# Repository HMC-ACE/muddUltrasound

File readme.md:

Low-Cost Underwater Ultrasonic Phased Array Research Platform
-------------------------------------------------------------

This repo contains all PCB designs, SAM4s MCU firmware, python imaging code, and documentation for the phased array research platform.

For full documentation, see [link](doc/build/html/index.html) (in a browser, you'll need to clone the repo first).

Directory
--------
 - `doc` contains the documentation source and build files (using sphinx).
 - `pcb` contains the KiCad PCB files for the channel boards and center board.
 - `mcu` contains the Atmel Studio project files for the MCU firmware.
 - `scripts` contains all python scripts to be run on the host computer.

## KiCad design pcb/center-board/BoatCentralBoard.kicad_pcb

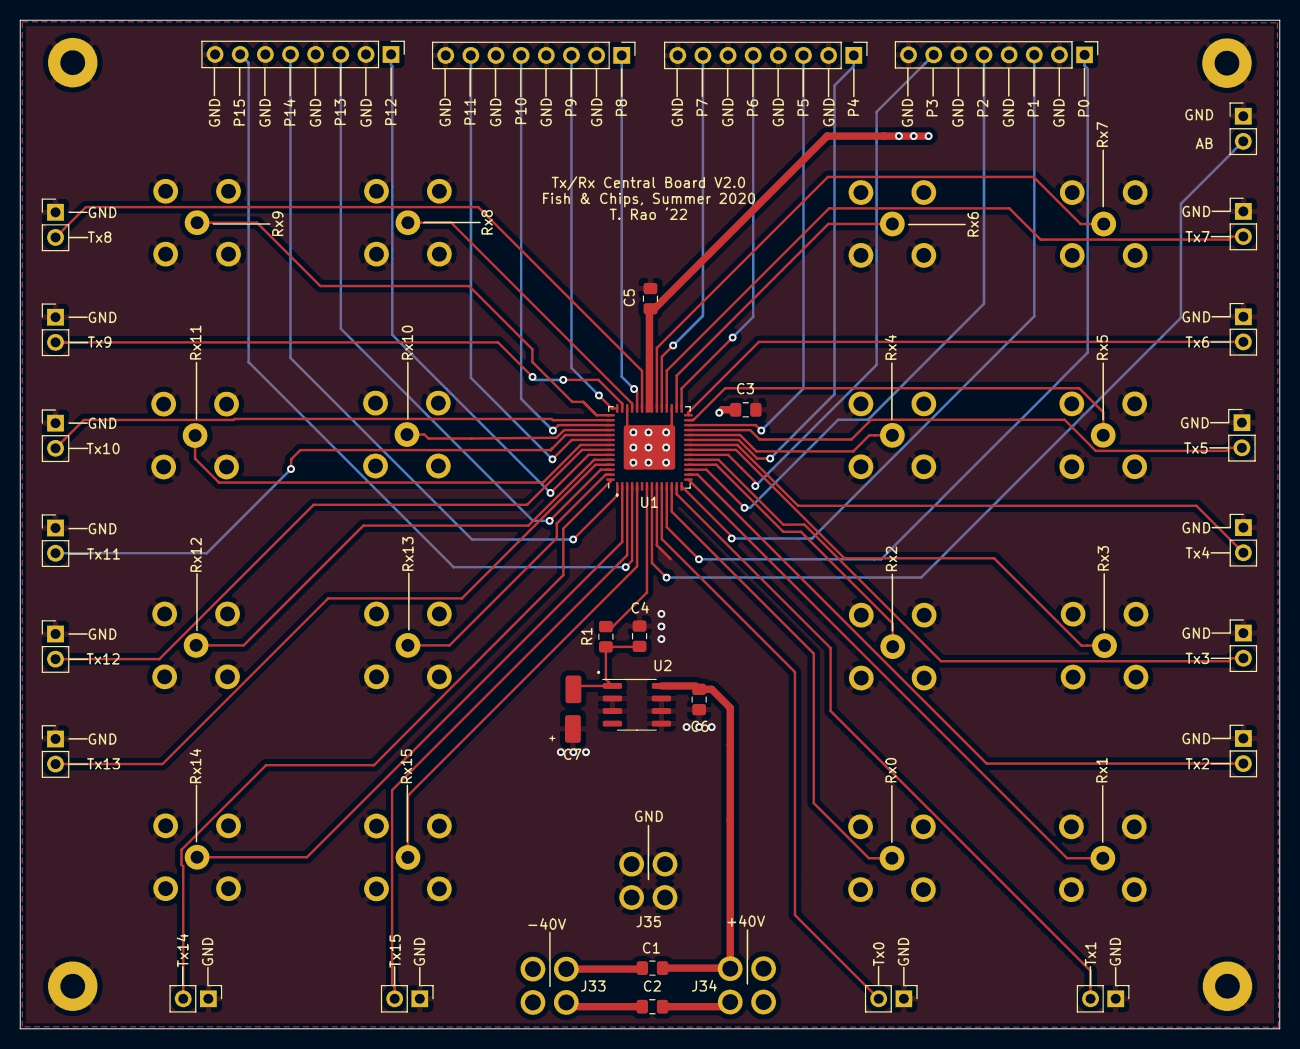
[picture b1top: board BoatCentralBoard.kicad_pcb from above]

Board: 4 copper layers, 127.2 x 101.9 mm, 50 parts (0 on the bottom side), 54 nets.

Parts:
C1: 1μF; C_0805_2012Metric_Pad1.15x1.40mm_HandSolder
C2, C3, C4, C5: 0.1μF; C_0805_2012Metric_Pad1.15x1.40mm_HandSolder
C6: 0.1uF; C_0805_2012Metric_Pad1.15x1.40mm_HandSolder
C7: 47uF; 47uFBypass
J1, J3, J5, J7, J9, J11, J13, J15, J17, J19, J21, J23, J25, J27, J29, J31: Screw_Terminal_01x02; PinHeader_1x02_P2.54mm_Vertical
J2, J4, J6, J8, J10, J12, J14, J16, J18, J20, J22, J24, J26, J28, J30, J32: Conn_Coaxial; BNC_Vertical_Custom
J33, J34, J35: Conn_01x01; Banana_Jack_4Pin
J36, J37, J38, J39: Screw_Terminal_01x08; Pin_Header_Straight_1x08_Pitch2.54mm
J40: Screw_Terminal_01x02; Pin_Header_Straight_1x02_Pitch2.54mm
R1: 1k; R_0805_2012Metric_Pad1.15x1.40mm_HandSolder
U1: HV2808; QFN-56-1EP_8x8mm_P0.5mm_EP4.5x5.2mm
U2: LM2936HVBMAX-3.3; SOIC-8_3.9x4.9mm_P1.27mm

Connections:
0SW0: J1.2, U1.10
0SW1: J2.1, U1.12
0SW2: J3.2, U1.13
0SW3: J4.1, U1.15
0SW4: J5.2, U1.16
0SW5: J6.1, U1.18
0SW6: J7.2, U1.19
0SW7: J8.1, U1.21
0SW8: J9.2, U1.22
0SW9: J10.1, U1.24
0SW10: J11.2, U1.25
0SW11: J12.1, U1.27
0SW12: J13.2, U1.28
0SW13: J14.1, U1.30
0SW14: J15.2, U1.32
0SW15: J16.1, U1.34
0SW16: J17.2, U1.37
0SW17: J18.1, U1.39
0SW18: J19.2, U1.41
0SW19: J20.1, U1.43
0SW20: J21.2, U1.44
0SW21: J22.1, U1.46
0SW22: J23.2, U1.47
0SW23: J24.1, U1.49
0SW24: J25.2, U1.50
0SW25: J26.1, U1.52
0SW26: J27.2, U1.53
0SW27: J28.1, U1.55
0SW28: J29.2, U1.56
0SW29: J30.1, U1.2
0SW30: J31.2, U1.3
0SW31: J32.1, U1.5
0Y01: J36.1, U1.11
0Y23: J36.3, U1.14
0Y45: J36.5, U1.17
0Y67: J36.7, U1.20
0Y89: J37.1, U1.23
0Y1011: J37.3, U1.26
0Y1213: J37.5, U1.29
0Y1415: J37.7, U1.33
0Y1617: J38.1, U1.38
0Y1819: J38.3, U1.42
0Y2021: J38.5, U1.45
0Y2223: J38.7, U1.48
0Y2425: J39.1, U1.51
0Y2627: J39.3, U1.54
0Y2829: J39.5, U1.1
0Y3031: J39.7, U1.4
3.3: C4.1, C7.2, R1.2, U2.1
+40V: C1.1, C2.1, C5.1, C6.1, J34.1, U1.35, U1.36, U2.8
-40V: C1.2, C2.2, C3.1, J33.1, U1.31, U1.40, U1.57
AB: J40.2, U1.8
GND: C3.2, C4.2, C5.2, C6.2, C7.1, J1.1, J2.2, J3.1, J4.2, J5.1, J6.2, J7.1, J8.2, J9.1, J10.2, J11.1, J12.2, J13.1, J14.2, J15.1, J16.2, J17.1, J18.2, J19.1, J20.2, J21.1, J22.2, J23.1, J24.2, J25.1, J26.2, J27.1, J28.2, J29.1, J30.2, J31.1, J32.2, J35.1, J36.2, J36.4, J36.6, J36.8, J37.2, J37.4, J37.6, J37.8, J38.2, J38.4, J38.6, J38.8, J39.2, J39.4, J39.6, J39.8, J40.1, U1.9, U2.2, U2.3, U2.5, U2.6, U2.7
VDD: R1.1, U1.7

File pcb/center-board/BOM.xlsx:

Component | Reference | Vendor | Vendor Part Number | Quantity Per Board | Cost for 1 | Cost for Board
Tx/Rx Switch | U1 | Microchip | HV2808K6-G | 1.0 | 17.53 | 17.53
3.3V Regulator | U2 | Digi-Key | LM2936HVBMAX3.3/NOPBCT-ND | 1.0 | 1.93 | 1.93
0.1uF SMD Capacitor | C2, C3, C4, C5, C6 | Digi-Key | 311-2083-1-ND | 6.0 | 0.2 | 1.2
1uF SMD Capacitor | C1 | Digi-Key | GRJ21BC72A105KE11L | 2.0 | 0.51 | 1.02
47uF SMD Electrolytic Capacitor | C7 | Digi-Key | 493-2225-1-ND | 1.0 | 0.5 | 0.5
1kΩ SMD Resistor | R1 | Digi-Key | 311-1.00KCRCT-ND | 1.0 | 0.01 | 0.01
±40V Banana Jack (Red) | J33, J34 | Digi-Key | CT3151V1-2-ND | 2.0 | 2.05 | 4.1
GND Banana Jack (Black) | J35 | Digi-Key | CT3151V1-0-ND | 1.0 | 2.05 | 2.05
Vertical BNC Connector | J2, J4, J6, J8, J10, J12, J14, J16, J18, J20, J22, J24, J26, J28, J30, J32 | Digi-Key | ACX1051-ND | 16.0 | 2.83 | 45.28
Screw Terminal Block, 2-Pin | J1, J3, J5, J7, J9, J11, J13, J15, J17, J19, J21, J23, J25, J27, J29, J31 | Pololu | 2491.0 | 17.0 | 2.02 | 34.34
Screw Terminal Block, 8-Pin | J36, J37, J38, J39 | Polou | 2497.0 | 4.0 | 2.02 | 8.08
 |  |  |  |  |  | 116.04

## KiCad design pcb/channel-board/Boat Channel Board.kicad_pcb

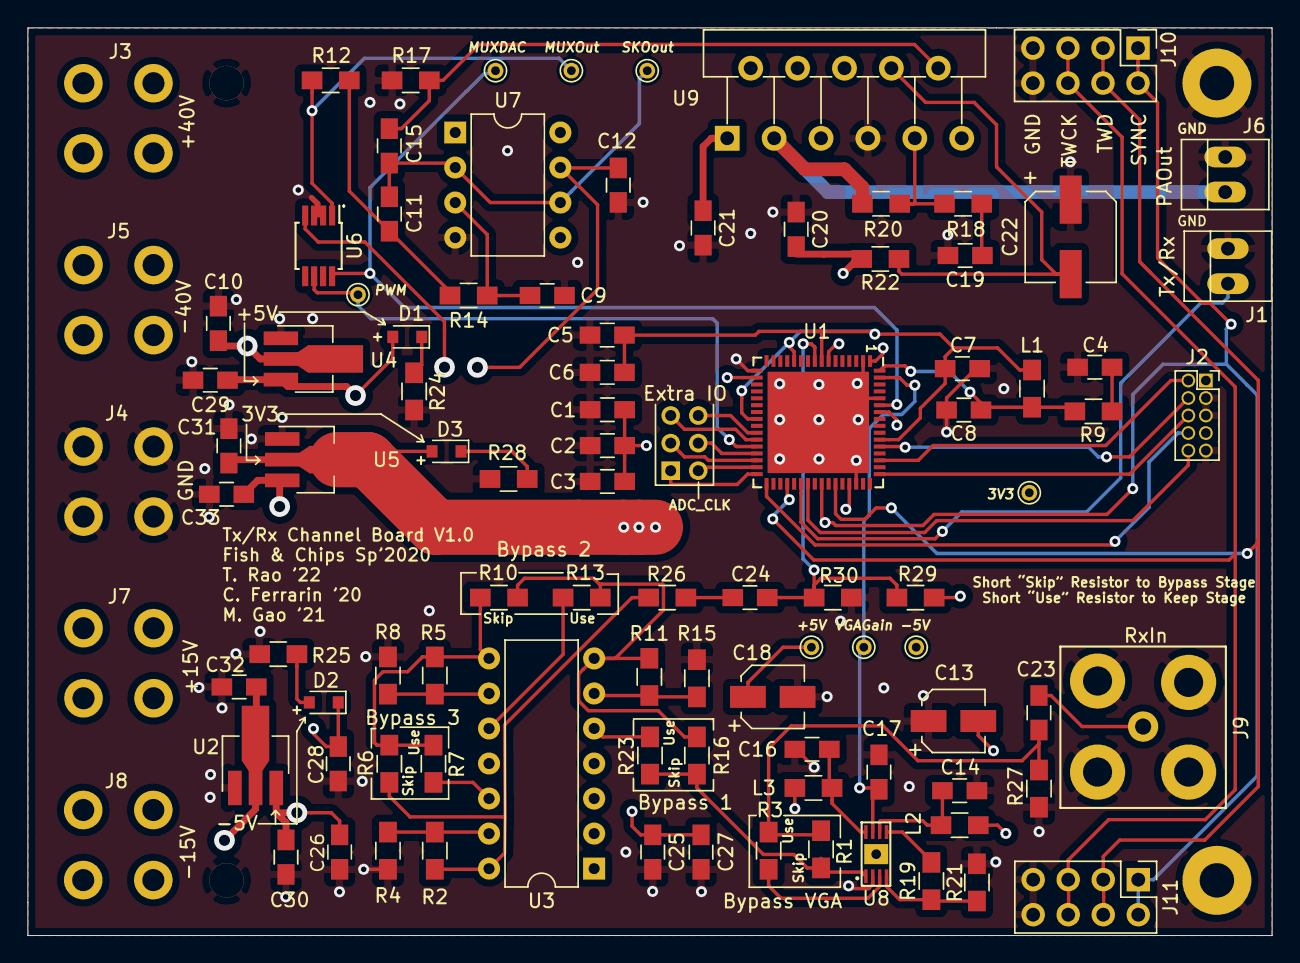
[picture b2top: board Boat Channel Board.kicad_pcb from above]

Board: 4 copper layers, 90.2 x 65.8 mm, 98 parts (1 on the bottom side), 60 nets.

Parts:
3V3: PINTST
+5V: PINTST
-5V: PINTST
C1, C23: 10nF; C_0805_HandSoldering
C2, C3, C6, C7, C8, C25, C26: 100nF; C_0805_HandSoldering
C4: 4.7uF; C_0805_HandSoldering
C5: 2.2uF; C_0805_HandSoldering
C9: 10pF; C_0805_HandSoldering
C10, C33: 1uF; C_0805_HandSoldering
C11: 2.2nF; C_0805_HandSoldering
C12, C14, C16, C20, C21: 0.1µF; C_0805_HandSoldering
C13, C18: 10µF; CP_Elec_4x5.7
C15: 910pF; C_0805_HandSoldering
C17: 1nF; C_0805_HandSoldering
C19, C31: 22µF; C_0805_HandSoldering
C22: 100µF; CP_Elec_6.3x5.7
C24: 0.1μF; C_0805_HandSoldering
C27, C28, C30, C32: 0.1uF; C_0805_HandSoldering
C29: 10uF; C_0805_HandSoldering
D1, D2, D3: LED; D_0805
J1: TX/RX Switch; PINHEAD1-2
J2: Conn_02x05_Odd_Even; Socket_Strip_Straight_2x05_Pitch1.27mm
J3, J4, J5, J7, J8: Conn_01x01; Banana_Jack_4Pin
J6: Piezo; PINHEAD1-2
J9: Conn_Coaxial; BNC_Socket_TYCO-AMP_LargePads
J10, J11: Conn_02x04_Row_Letter_Last; Pin_Header_Straight_2x04_Pitch2.54mm
J12: Conn_01x06; Pin_Header_Straight_2x03_Pitch2.00mm
L1: 10uH; L_0805_HandSoldering
L2, L3: 120nH; L_0805_HandSoldering
MUXDAC: PINTST
MUXOut: PINTST
PWM: PINTST
R1, R3, R6, R7, R10, R13, R16, R23: 0Ω; R_0805_HandSoldering
R2, R5, R11, R17: 10kΩ; R_0805_HandSoldering
R4, R8, R15, R18, R27, R29, R30: 1kΩ; R_0805_HandSoldering
R9: 1; R_0805_HandSoldering
R12, R20: 20kΩ; R_0805_HandSoldering
R14: 6.98kΩ; R_0805_HandSoldering
R19, R21: 100Ω; R_0805_HandSoldering
R22: 15kΩ; R_0805_HandSoldering
R24, R25: 300Ω; R_0805_HandSoldering
R26: 1k; R_0805_HandSoldering
R28: 120Ω; R_0805_HandSoldering
SKOout: PINTST
U1: SAM4S4B; QFN-64-1EP_9x9mm_Pitch0.5mm
U2: L79L05_SOT89; SOT-89-3_Handsoldering
U3: TL084CP; DIP-14_W7.62mm
U4: ZXTR2005Z-13; SOT-89-3_Handsoldering
U5: AZ1117CH-3.3TRG1; SOT-89-3_Handsoldering
U6: MAX4644; MSOP-8_3x3mm_Pitch0.65mm
U7: MCP601-xP; DIP-8_W7.62mm
U8: AD8337; AD8337_LFCSP8_3x3
U9: LM3886T; TO-220-11_Vertical_StaggeredType1
VGAGain: PINTST

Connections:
3.3V: C1.2, C2.2, C3.2, C31.1, D3.2, J2.1, R29.1, U1.1, U1.7, U1.18, U1.45, U1.58, U5.2
+5V: +5V.1, C12.2, C18.1, C25.1, C27.2, C29.2, D1.2, L3.1, U3.4, U4.3, U6.4, U7.7
+15V: C10.2, C33.2, J7.1, U4.2, U5.3
+40V: C21.1, J3.1, U9.1, U9.5
-5V: -5V.1, C13.2, C26.1, C28.2, C30.2, D2.1, L2.1, U2.3, U3.11
-15V: C32.1, J8.1, U2.2
-40V: C20.2, J5.1, R22.2, U9.4
/IN+: C15.1, R17.1, U9.10
/PrAin+: R3.2, U8.3
/PrAin-: R19.1, R21.1, U8.4
/Vin+: C9.1, R14.1, U7.3
ADC_CLK: J12.2, U1.31
ADCin: C24.1, R29.2, R30.1, U1.9
ExtraIO1: J12.1, U1.32
ExtraIO3: J12.3, U1.30
ExtraIO4: J12.4, U1.29
ExtraIO5: J12.5, U1.27
ExtraIO6: J12.6, U1.26
GND: C1.1, C2.1, C3.1, C4.1, C5.1, C6.1, C7.1, C8.1, C9.2, C10.1, C12.1, C13.1, C14.2, C16.2, C17.1, C18.2, C19.2, C20.1, C21.2, C22.1, C25.2, C26.2, C27.1, C28.1, C29.1, C30.1, C31.2, C32.2, C33.1, J1.2, J2.3, J2.5, J2.9, J4.1, J6.2, J9.2, J10.7, J10.8, J11.7, J11.8, R4.1, R8.1, R15.1, R17.2, R21.2, R24.2, R25.2, R27.2, R28.2, R30.2, U1.2, U1.17, U1.46, U1.60, U1.65, U2.1, U4.1, U5.1, U6.2, U6.3, U7.4, U8.2, U9.7
GainIn: R1.2, R16.1, R23.1, U8.1
MUXOut: MUXOut.1, R12.2, U6.1
MUX_DAC: MUXDAC.1, U1.59, U6.8
unnamed: C4.2, R9.2
unnamed: C11.2, R12.1, R14.2
unnamed: C14.1, L2.2, U8.6
unnamed: C16.1, L3.2, U8.8
unnamed: C19.1, R18.2
unnamed: C22.2, R22.1, U9.8
unnamed: C23.1, J9.1
unnamed: C23.2, R1.1, R3.1, R27.1
unnamed: C24.2, R26.1
unnamed: D1.1, R24.1
unnamed: D2.2, R25.1
unnamed: D3.1, R28.1
unnamed: R2.1, R4.2, U3.13
unnamed: R2.2, R6.2, R26.2, U3.14
unnamed: R5.1, R8.2, U3.9
unnamed: R7.2, U3.12
unnamed: R10.1, R11.2, R13.1, R16.2, U3.7
unnamed: R5.2, R6.1, R7.1, R10.2, U3.8
unnamed: R11.1, R15.2, U3.6
unnamed: R13.2, U3.10
unnamed: R18.1, R20.2, U9.9
unnamed: R19.2, U8.5
unnamed: R23.2, U3.5
PAOut: J6.1, R20.1, U9.3
PWM: PWM.1, U1.28, U6.6
SAMNRST: J2.10, U1.39
SAMTCK: J2.4, U1.53
SAMTDI: J2.8, U1.33
SAMTDO: J2.6, U1.49
SAMTMS: J2.2, U1.51
SKOut: C11.1, C15.2, SKOout.1, U7.2, U7.6
SYNC: J10.1, J10.2, J11.1, J11.2, U1.41
TWCK: J10.5, J10.6, J11.5, J11.6, U1.36
TWD: J10.3, J10.4, J11.3, J11.4, U1.43
TXRX: J1.1, U1.38
VDDCORE: C5.2, C6.2, C7.2, L1.1, U1.8, U1.12, U1.24, U1.54
VDDPLL: C8.2, L1.2, R9.1, U1.64
VGAGain: C17.2, U1.63, U8.7, VGAGain.1

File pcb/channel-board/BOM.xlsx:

Category | Component | Reference | Value | Package | Vendor | Vendor Part Number | Quantity Per Board | Cost for 1 Part | Total Cost per Board | Vendor Description
ICs | ATSAM4S4B MCU | U1 |  | QFN-64, 9x9mm, 0.5mm Pitch | Digi-Key | ATSAM4S4BA-MU-ND | 1.0 | 3.82 | 3.82 | IC MCU 32BIT 256KB FLASH 64QFN
 | -5V Voltage Regulator | U2 |  | SOT-89-3 | Digi-Key | MC79L05F-TPMSCT-ND | 1.0 | 0.38 | 0.38 | IC REG LINEAR -5V 100MA SOT89
 | TL084CP Quad Op Amp | U3 |  | DIP-14 | Digi-Key | 296-12951-5-ND | 1.0 | 1.52 | 1.52 | Operational Amplifiers - Op Amps Quad JFET Neg Input
 | +5V Voltage Regulator | U4 |  | SOT-89-3 | Digi-Key | ZXTR2005Z-13DICT-ND | 1.0 | 0.53 | 0.53 | IC REG LINEAR 5V 38MA SOT89
 | 3.3V Voltage Regulator | U5 |  | SOT-89-3 | Digi-Key | AZ1117CR-3.3TRG1DICT-ND | 1.0 | 0.38 | 0.38 | IC REG LINEAR 3.3V 600MA SOT89-3
 | MAX4644 MUX | U6 |  | MSOP-8, 3x3mm, 0.65mm Pitch | Digi-Key | MAX4644EUA+-ND | 1.0 | 2.15 | 2.15 | IC SWITCH SPDT 8UMAX
 | MCP601 Op Amp | U7 |  | DIP-8 | Digi-Key | MCP601-E/P-ND | 1.0 | 0.48 | 0.48 | IC OPAMP GP 1 CIRCUIT 8DIP
 | AD8337 VGA | U8 |  | LFCSP-8, 3x3mm, 0.5mm Pitch | Digi-Key | AD8337BCPZ-REEL7CT-ND | 1.0 | 6.19 | 6.19 | IC VGAIN AMP 8LFCSP
 | LM3886T Power Amplifier | U9 |  | TO-220-11 | Digi-Key | LM3886T/NOPB-ND | 1.0 | 6.82 | 6.82 | IC AMP CLSS AB MONO 68W TO220-11
Power Indication | 300Ω SMD Resistor | R24, R25 | 300Ω | Hand Solder 0805 | Digi-Key | 311-300CRCT-ND | 2.0 | 0.1 | 0.2 | RES SMD 300 OHM 1% 1/8W 0805
 | 120Ω SMD Resistor | R28 | 120Ω | Hand Solder 0805 | Digi-Key | 311-120CRCT-ND | 1.0 | 0.1 | 0.1 | RES SMD 120 OHM 1% 1/8W 0805
 | Green SMD LED | D1, D2, D3 |  | Hand Solder 0805 | Digi-Key | 296-12951-5-ND | 3.0 | 0.59 | 1.77 | Standard LEDs - SMD AlInGaP Green
Power Sequencing | 10nF SMD Capacitor | C1, C23 | 10nF | Hand Solder 0805 | Digi-Key | 311-1475-1-ND | 2.0 | 0.12 | 0.24 | 10000pF ±10% 100V Ceramic Capacitor X7R 0805 (2012 Metric)
 | 4.7uF SMD Capacitor | C4 | 4.7uF | Hand Solder 0805 | Digi-Key | 490-12753-1-ND | 1.0 | 0.25 | 0.25 | 4.7µF ±10% 25V Ceramic Capacitor X5R 0805 (2012 Metric)
 | 2.2uF SMD Capacitor | C5 | 2.2uF | Hand Solder 0805 | Digi-Key | 490-14467-1-ND | 1.0 | 0.22 | 0.22 | 2.2µF ±10% 25V Ceramic Capacitor X7R 0805 (2012 Metric)
 | 10uH SMD Inductor | L1 | 10uH | Hand Solder 0805 | Digi-Key | 445-8656-1-ND | 1.0 | 0.16 | 0.16 | 10µH Shielded Multilayer Inductor 300mA 680mOhm 0805 (2012 Metric)
 | 1Ω SMD Resistor | R9 | 1Ω | Hand Solder 0805 | Digi-Key | 311-1.00CRCT-ND | 1.0 | 0.1 | 0.1 | RES SMD 1 OHM 1% 1/8W 0805
Connectors | Screw Terminal 1x2 | J1, J6 |  | Screw Terminal Block 2-Pin | Digi-Key | A98333-ND | 1.0 | 0.92 | 0.92 | 2 Position Wire to Board Terminal Block Horizontal with Board 0.100" (2.54mm) T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
 | JTAG-10 Pin | J2 |  | Pin header 2x5 1.27mm | Digi-Key | 612-FTSH-105-01-F-D-K-ND | 1.0 | 3.99 | 3.99 | CONN HEADER VERT 10POS 1.27MM
 | Power Banana Jacks | J3, J4, J5, J7, J8 | ±40, ±15 | 4-Pin Banana Jack Red | Digi-Key | BKCT3151SP-2-ND | 5.0 | 2.05 | 10.25 | CONN BANANA JACK SOLDER RED
 | Rx In BNC Connector | J9 |  | Right-Angle Coaxial Connector | Digi-Key | A97570-ND | 1.0 | 2.91 | 2.91 | CONN BNC JACK R/A 50 OHM PCB
 | DIP-14 Socket | U3 |  | DIP-14 | Digi-Key | AE9989-ND | 1.0 | 0.22 | 0.22 | CONN IC DIP SOCKET 14POS TIN
 | DIP-8 Socket | U7 |  | DIP-8 | Digi-Key | AE9986-ND | 1.0 | 0.18 | 0.18 | CONN IC DIP SOCKET 8POS TIN
 | Pin Headers, 2x4 for Ribbon | J10, J11 |  | Pin Headers 2x40, 2.54mm Pitch | Digi-Key | 609-3203-ND | 2.0 | 0.47 | 0.94 | CONN HEADER R/A 40POS 2.54MM
Tx/Rx Amplifiers | 0Ω SMD Resistor | R1, R3, R6, R7, R10, R13, R16, R23 | 0Ω | Hand Solder 0805 | Digi-Key | 311-0.0ARCT-ND | 8.0 | 0.1 | 0.8 | RES SMD 0 OHM JUMPER 1/8W 0805
 | 20kΩ SMD Resistor | R12, R20 | 20kΩ | Hand Solder 0805 | Digi-Key | 311-20.0KCRCT-ND | 2.0 | 0.1 | 0.2 | RES SMD 20K OHM 1% 1/8W 0805
 | 6.98kΩ SMD Resistor | R14 | 6.98kΩ | Hand Solder 0805 | Digi-Key | 311-6.98KCRCT-ND | 1.0 | 0.1 | 0.1 | RES SMD 6.98K OHM 1% 1/8W 0805
 | 10kΩ SMD Resistor | R2, R5, R11, R17 | 10kΩ | Hand Solder 0805 | Digi-Key | 311-10.0KCRCT-ND | 4.0 | 0.1 | 0.4 | RES SMD 10K OHM 1% 1/8W 0805
 | 1kΩ SMD Resistor | R4, R8, R15, R18, R26, R27, R29, R30 | 1kΩ | Hand Solder 0805 | Digi-Key | 311-1.00KCRCT-ND | 8.0 | 0.1 | 0.8 | RES SMD 1K OHM 1% 1/8W 0805
 | 100Ω SMD Resistor | R19, R21 | 100Ω | Hand Solder 0805 | Digi-Key | 311-100CRCT-ND | 2.0 | 0.1 | 0.2 | RES SMD 100 OHM 1% 1/8W 0805
 | 15kΩ SMD Resistor | R22 | 15kΩ | Hand Solder 0805 | Digi-Key | 311-15.0KCRCT-ND | 1.0 | 0.1 | 0.1 | RES SMD 15K OHM 1% 1/8W 0805
 | 10pf SMD Capacitor | C9 | 10pF | Hand Solder 0805 | Digi-Key | 311-1834-1-ND | 1.0 | 0.15 | 0.15 | CAP CER 10PF 100V C0G/NPO 0805
 | 2.2nF SMD Capacitor | C11 | 2.2nF | Hand Solder 0805 | Digi-Key | 311-1479-1-ND | 1.0 | 0.12 | 0.12 | CAP CER 2200PF 100V X7R 0805
 | 0.1uF SMD Capacitor | C2, C3, C6, C7, C8, C12, C14, C16, C20, C21, C24, C25, C26, C27, C28, C30, C32 | 0.1uF | Hand Solder 0805 | Digi-Key | 311-2083-1-ND | 17.0 | 0.2 | 3.4 | CAP CER 0.1UF 100V X7R 0805
 | 0.1uF SMD Electrolytic Cap | C20, C21 | 0.1uF | 4x5.7 electrolytic shell | Digi-Key | 732-8266-1-ND | 2.0 | 0.17 | 0.34 | 0.1µF 50V Aluminum Electrolytic Capacitors Radial, Can - SMD 5000 Hrs @ 105°C
 | 10uF SMD Electrolytic Cap | C13, C18 | 10uF | 4x5.7 electrolytic shell | Digi-Key | 732-8503-1-ND | 2.0 | 0.19 | 0.38 | 10µF 35V Aluminum Electrolytic Capacitors Radial, Can - SMD 2000 Hrs @ 105°C
 | 10uF SMD Capacitor | C29 | 10uF | Hand Solder 0805 | Digi-Key | 399-C0805C106K8PAC7210CT-ND | 1.0 | 0.14 | 0.14 | CAP CER 10UF 10V X5R 0805
 | 1uF SMD Capacitor | C10, C33 | 1uF | Hand Solder 0805 | Digi-Key | 399-C0805C105J3REC7800CT-ND | 2.0 | 0.13 | 0.26 | CAP CER 0805 1UF 25V X7R 5%
 | 910pF SMD Capacitor | C15 | 910pF | Hand Solder 0805 | Digi-Key | 478-12759-1-ND | 1.0 | 0.29 | 0.29 | CAP CER 910PF 100V X7R 0805
 | 1nF SMD Capacitor | C17 | 1nF | Hand Solder 0805 | Digi-Key | 311-1472-1-ND | 1.0 | 0.13 | 0.13 | CAP CER 1000PF 100V X7R 0805
 | 22uF SMD Capacitor | C19, C31 | 22uF | Hand Solder 0805 | Digi-Key | 490-9951-1-ND | 2.0 | 0.46 | 0.92 | CAP CER 22UF 10V X5R 0805
 | 100uF SMD Electrolytic Cap | C22 | 100uF | 6.3x5.7 electrolytic shell | Digi-Key | 493-2105-1-ND | 1.0 | 0.3 | 0.3 | CAP ALUM 100UF 20% 16V SMD
 | 120nH SMD Inductor | L2, L3 | 120nH | Hand Solder 0805 | Digi-Key | 445-8984-1-ND | 2.0 | 0.18 | 0.36 | 120nH Shielded Multilayer Inductor 300mA 200mOhm Max 0805 (2012 Metric)
Equipment | Heat Sink | N/A |  | TO-220 | Digi-Key | 590302B03600G-ND | 1.0 | 1.03 | 1.03

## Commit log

2022-10-09 commit mcu, readme and scripts
2022-10-10 commit pcb & doc
2023-03-11 Add MIT License
2023-03-16 fix crash if visualization is off or if `data/` is missing
